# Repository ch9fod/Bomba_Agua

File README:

Basic on/off switch with rele using a PIC12F609

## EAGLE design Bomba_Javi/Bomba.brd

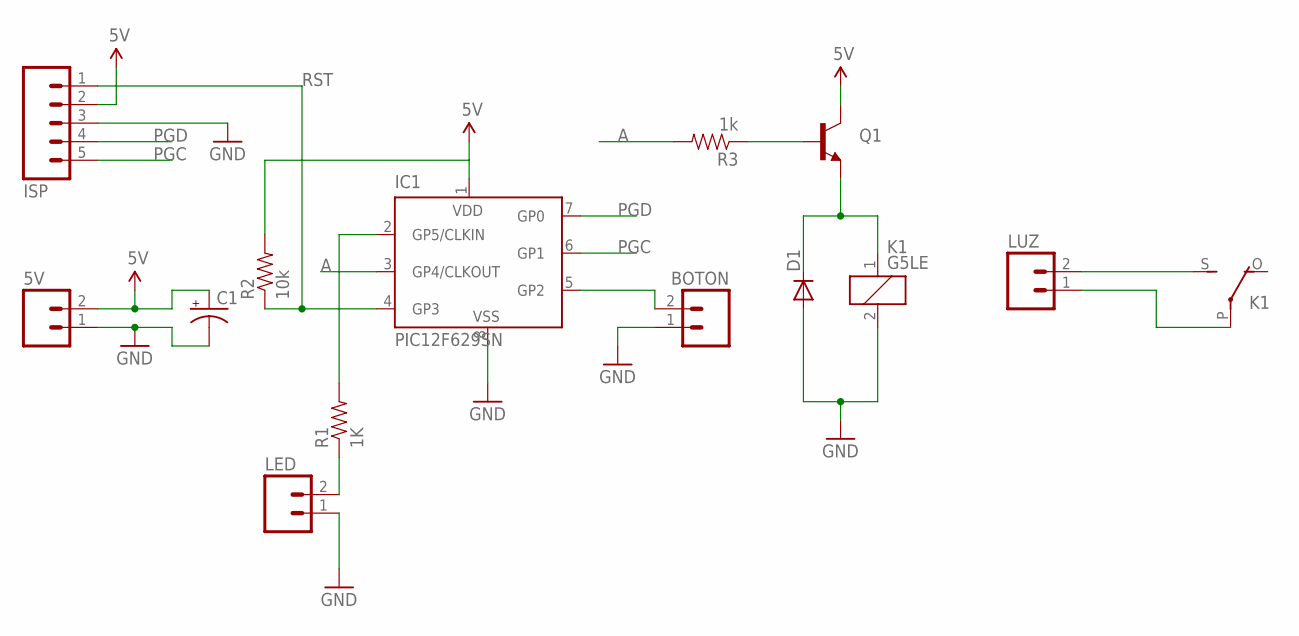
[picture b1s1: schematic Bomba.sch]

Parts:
5V: M025MM; SCREWTERMINAL-5MM-2
BOTON: M025MM; SCREWTERMINAL-5MM-2
C1: CAP_POLPTH1; CPOL-RADIAL-100UF-25V
D1: DIODE1N4148; DIODE-1N4148
IC1: PIC12F629SN; SO-08
ISP: M05LOCK_LONGPADS; 1X05_LOCK_LONGPADS
K1: G5LE
LED: M02LOCK_LONGPADS; 1X02_LOCK_LONGPADS
LUZ: M025MM; SCREWTERMINAL-5MM-2
Q1: TRANSISTOR_NPNSOT23; SOT23
R1: 1K; 1206
R2: 10k; 1206
R3: 1k; 1206

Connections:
5V: 5V.2, C1.1 (+), IC1.1 (VDD), ISP.2, Q1.3 (C), R2.2
A: IC1.3 (GP4/CLKOUT), R3.2
GND: 5V.1, BOTON.1, C1.2 (-), D1.A, IC1.8 (VSS), ISP.3, K1.2, LED.1
unnamed: D1.C, K1.1, Q1.2 (E)
unnamed: BOTON.2, IC1.5 (GP2)
unnamed: Q1.1 (B), R3.1
unnamed: K1.S, LUZ.2
unnamed: K1.P, LUZ.1
unnamed: IC1.2 (GP5/CLKIN), R1.2
unnamed: LED.2, R1.1
PGC: IC1.6 (GP1), ISP.5
PGD: IC1.7 (GP0), ISP.4
RST: IC1.4 (GP3), ISP.1, R2.1

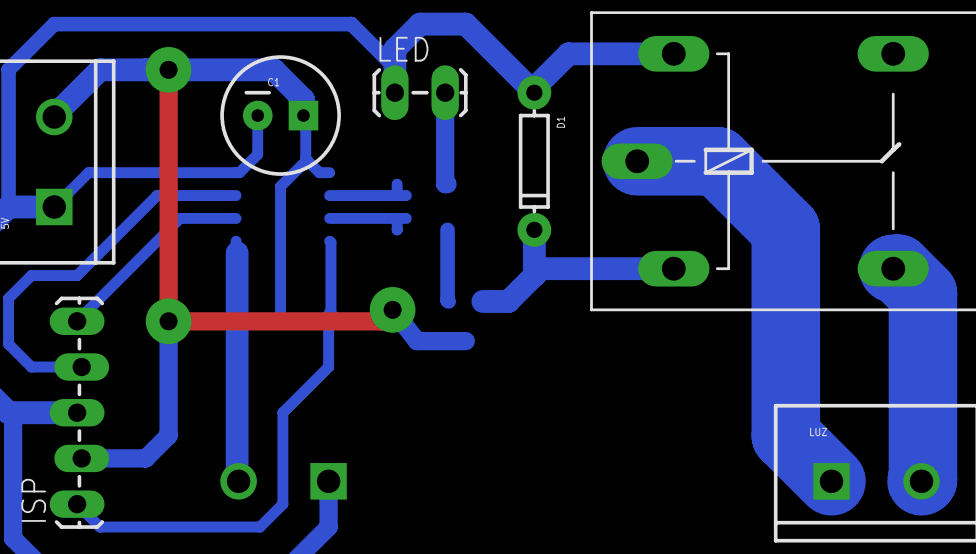
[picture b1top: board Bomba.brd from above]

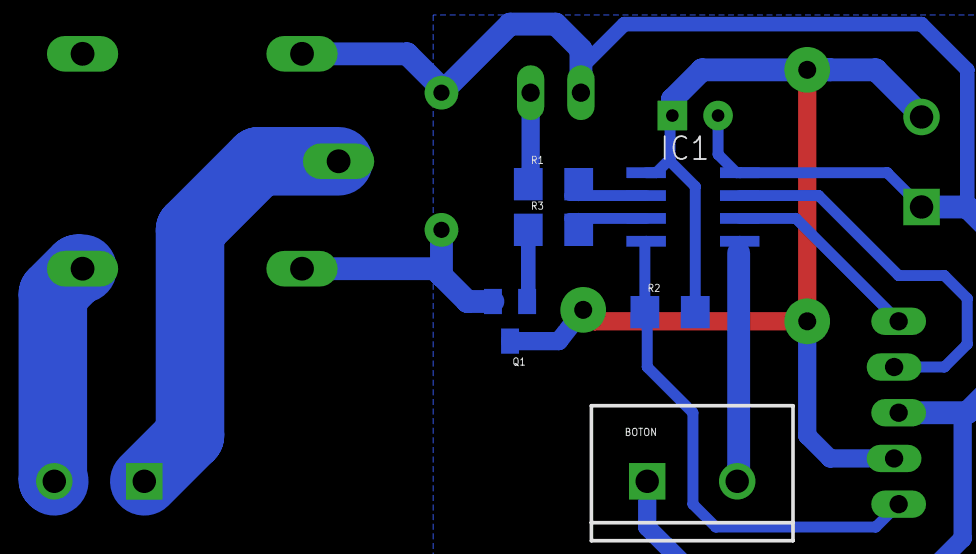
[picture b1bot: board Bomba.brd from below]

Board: 2 copper layers, 13 parts (6 on the bottom side), 13 nets.

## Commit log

2012-10-05 First code with ext int
2012-10-05 Primer ReadME
2012-10-05 Borrar archivos que no sirven
2012-10-08 Ext INT working and delays
2012-10-08 delay_Xm ready
2012-10-10 Eagle files
2012-10-12 Pcb continuado
2012-10-15 PCB terminado. PDF

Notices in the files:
parts and their libraries:
SparkFun-Connectors: Licensing: CC v3.0 Share-Alike You are welcome to use this library for commercial purposes.
